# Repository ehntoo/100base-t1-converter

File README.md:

# 100base-t1-converter

This project provides a media converter for connecting 100Base-TX ethernet to
100Base-T1 (Automotive Ethernet) networks, using an NXP TJA1101 PHY. This part
doesn't have a whole lot of officially-available documentation, but is
significantly cheaper than the previous-generation TJA1100. Sufficient
information to use the chip in a design was assembled from various NXP (and
other) schematics online, such as the NXP schematics for the S32K148-T-BOX EVK.

Additional information for debugging was sourced from the Linux TJA11xx PHY
drivers.

The 100Base-TX PHY used is a CoreChips SR8201F (Realtek RTL8201F compatible),
sourceable from LCSC for ~$0.25 in reasonable quantities.

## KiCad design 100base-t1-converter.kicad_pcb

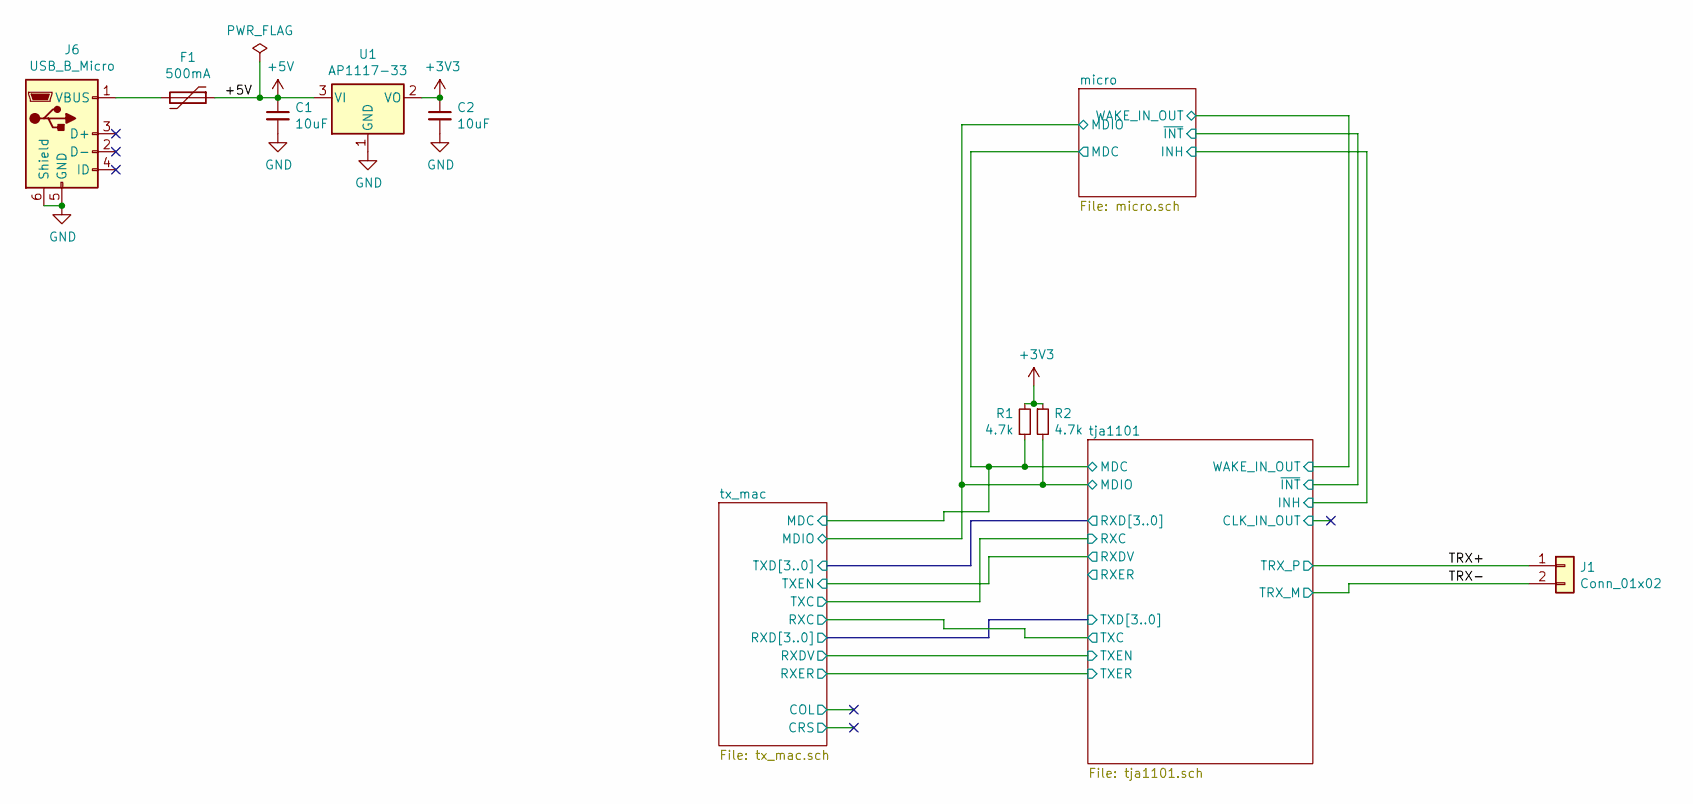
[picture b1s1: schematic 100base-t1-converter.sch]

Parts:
C1, C2: 10uF; C_0603_1608Metric_Pad1.05x0.95mm_HandSolder
F1: 500mA; Fuse_0805_2012Metric_Pad1.15x1.40mm_HandSolder
J1: Conn_01x02; SIP-2
J6: USB_B_Micro; LCSC_C77238
R1, R2: 4.7k; R_0603_1608Metric_Pad1.05x0.95mm_HandSolder
U1: AP1117-33; SOT-223-3_TabPin2

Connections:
+3V3: C2.1, R1.2, R2.1, U1.2 (VO); also elsewhere on the board
+5V: C1.1, F1.1, U1.3 (VI); also elsewhere on the board
/TRX+: J1.1; also elsewhere on the board
/TRX-: J1.2; also elsewhere on the board
/micro/MDC: R1.1; also elsewhere on the board
/micro/MDIO: R2.2; also elsewhere on the board
GND: C1.2, C2.2, J6.5 (GND), J6.6 (Shield), U1.1 (GND); also elsewhere on the board
unnamed: F1.2, J6.1 (VBUS)

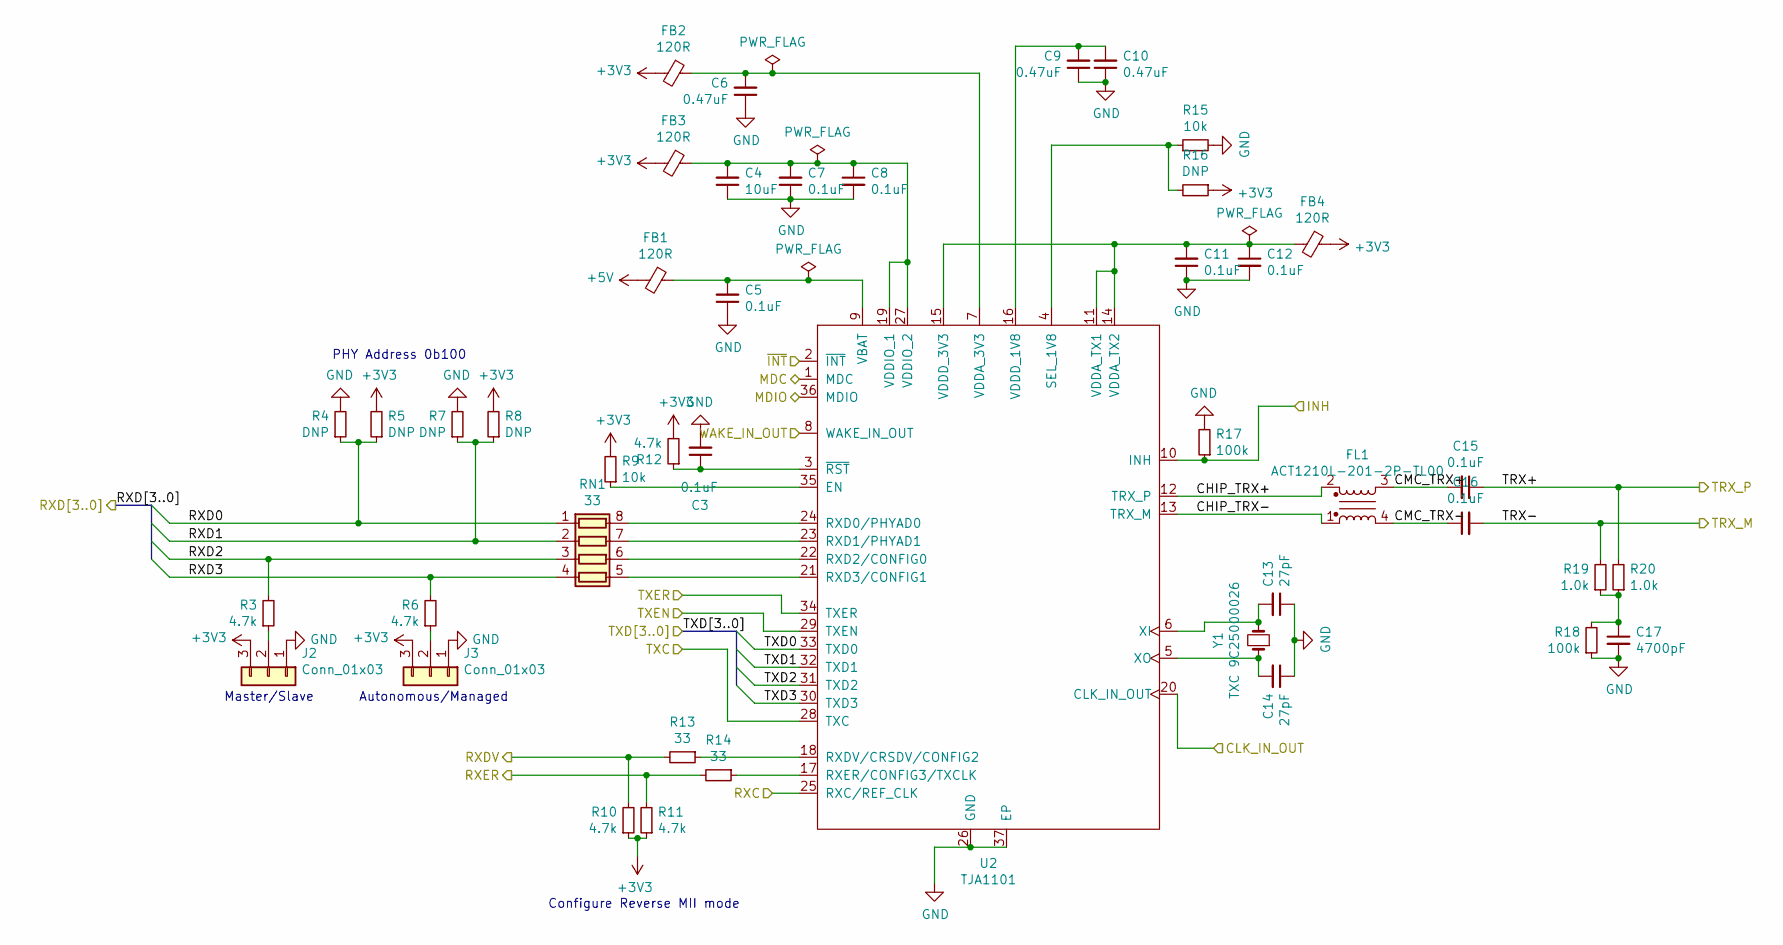
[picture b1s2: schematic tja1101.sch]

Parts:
C3, C5, C7, C8, C11, C12, C15, C16: 0.1uF; C_0603_1608Metric_Pad1.05x0.95mm_HandSolder
C4: 10uF; C_0603_1608Metric_Pad1.05x0.95mm_HandSolder
C6, C9, C10: 0.47uF; C_0603_1608Metric_Pad1.05x0.95mm_HandSolder
C13, C14: 27pF; C_0603_1608Metric_Pad1.05x0.95mm_HandSolder
C17: 4700pF; C_0603_1608Metric_Pad1.05x0.95mm_HandSolder
FB1, FB2, FB3, FB4: 120R; L_0603_1608Metric_Pad1.05x0.95mm_HandSolder
FL1: ACT1210L-201-2P-TL00; SOIC-4
J2, J3: Conn_01x03; PinSocket_1x03_P2.54mm_Vertical
R3, R6, R10, R11, R12: 4.7k; R_0603_1608Metric_Pad1.05x0.95mm_HandSolder
R4, R5, R7, R8, R16: DNP; R_0603_1608Metric_Pad1.05x0.95mm_HandSolder
R9, R15: 10k; R_0603_1608Metric_Pad1.05x0.95mm_HandSolder
R13, R14: 33; R_0603_1608Metric_Pad1.05x0.95mm_HandSolder
R17, R18: 100k; R_0603_1608Metric_Pad1.05x0.95mm_HandSolder
R19, R20: 1.0k; R_0603_1608Metric_Pad1.05x0.95mm_HandSolder
RN1: 33; R_Array_Convex_Reversed_4x0603
U2: TJA1101; QFN-36-1EP_6x6mm_P0.5mm_EP4.1x4.1mm_ThermalVias
Y1: TXC 9C25000026; Crystal_SMD_HC49-SD_HandSoldering

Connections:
+3V3: FB2.2, FB3.2, FB4.1, J2.3, J3.3, R5.2, R8.2, R9.2, R10.1, R11.1, R12.2, R16.1; also elsewhere on the board
+5V: FB1.2; also elsewhere on the board
/TRX+: C15.1, R20.2; also elsewhere on the board
/TRX-: C16.2, R19.2; also elsewhere on the board
/micro/INH: R17.1, U2.10 (INH); also elsewhere on the board
/micro/MDC: U2.1 (MDC); also elsewhere on the board
/micro/MDIO: U2.36 (MDIO); also elsewhere on the board
/micro/WAKE_IN_OUT: U2.8 (WAKE_IN_OUT); also elsewhere on the board
/micro/~INT: U2.2 (~INT); also elsewhere on the board
/tja1101/CHIP_TRX+: FL1.2, U2.12 (TRX_P)
/tja1101/CHIP_TRX-: FL1.1, U2.13 (TRX_M)
/tja1101/CLK_IN_OUT: U2.20 (CLK_IN_OUT)
/tja1101/CMC_TRX+: C15.2, FL1.3
/tja1101/CMC_TRX-: C16.1, FL1.4
/tja1101/RXC: U2.25 (RXC/REF_CLK); also elsewhere on the board
/tja1101/RXD0: R4.1, R5.1, RN1.1 (R1.1); also elsewhere on the board
/tja1101/RXD1: R7.1, R8.1, RN1.2 (R2.1); also elsewhere on the board
/tja1101/RXD2: R3.2, RN1.3 (R3.1); also elsewhere on the board
/tja1101/RXD3: R6.2, RN1.4 (R4.1); also elsewhere on the board
/tja1101/RXDV: R10.2, R13.2; also elsewhere on the board
/tja1101/RXER: R11.2, R14.2
/tx_mac/RXC: U2.28 (TXC); also elsewhere on the board
/tx_mac/RXD0: U2.33 (TXD0); also elsewhere on the board
/tx_mac/RXD1: U2.32 (TXD1); also elsewhere on the board
/tx_mac/RXD2: U2.31 (TXD2); also elsewhere on the board
/tx_mac/RXD3: U2.30 (TXD3); also elsewhere on the board
/tx_mac/RXDV: U2.29 (TXEN); also elsewhere on the board
/tx_mac/RXER: U2.34 (TXER); also elsewhere on the board
GND: C3.2, C4.1, C5.1, C6.1, C7.1, C8.2, C9.1, C10.1, C11.1, C12.2, C13.1, C14.1, C17.2, J2.1, J3.1, R4.2, R7.2, R15.2, R17.2, R18.1, U2.26 (GND), U2.37 (EP); also elsewhere on the board
unnamed: C3.1, R12.1, U2.3 (~RST)
unnamed: C4.2, C7.2, C8.1, FB3.1, U2.19 (VDDIO_1), U2.27 (VDDIO_2)
unnamed: C5.2, FB1.1, U2.9 (VBAT)
unnamed: C6.2, FB2.1, U2.7 (VDDA_3V3)
unnamed: C9.2, C10.2, U2.16 (VDDD_1V8)
unnamed: C11.2, C12.1, FB4.2, U2.11 (VDDA_TX1), U2.14 (VDDA_TX2), U2.15 (VDDD_3V3)
unnamed: C13.2, U2.6 (XI), Y1.2
unnamed: C14.2, U2.5 (XO), Y1.1
unnamed: C17.1, R18.2, R19.1, R20.1
unnamed: J2.2, R3.1
unnamed: J3.2, R6.1
unnamed: R9.1, U2.35 (EN)
unnamed: R13.1, U2.18 (RXDV/CRSDV/CONFIG2)
unnamed: R14.1, U2.17 (RXER/CONFIG3/TXCLK)
unnamed: R15.1, R16.2, U2.4 (SEL_1V8)
unnamed: RN1.5 (R4.2), U2.21 (RXD3/CONFIG1)
unnamed: RN1.6 (R3.2), U2.22 (RXD2/CONFIG0)
unnamed: RN1.7 (R2.2), U2.23 (RXD1/PHYAD1)
unnamed: RN1.8 (R1.2), U2.24 (RXD0/PHYAD0)

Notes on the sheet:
Configure Reverse MII mode
PHY Address 0b100
Master/Slave
Autonomous/Managed

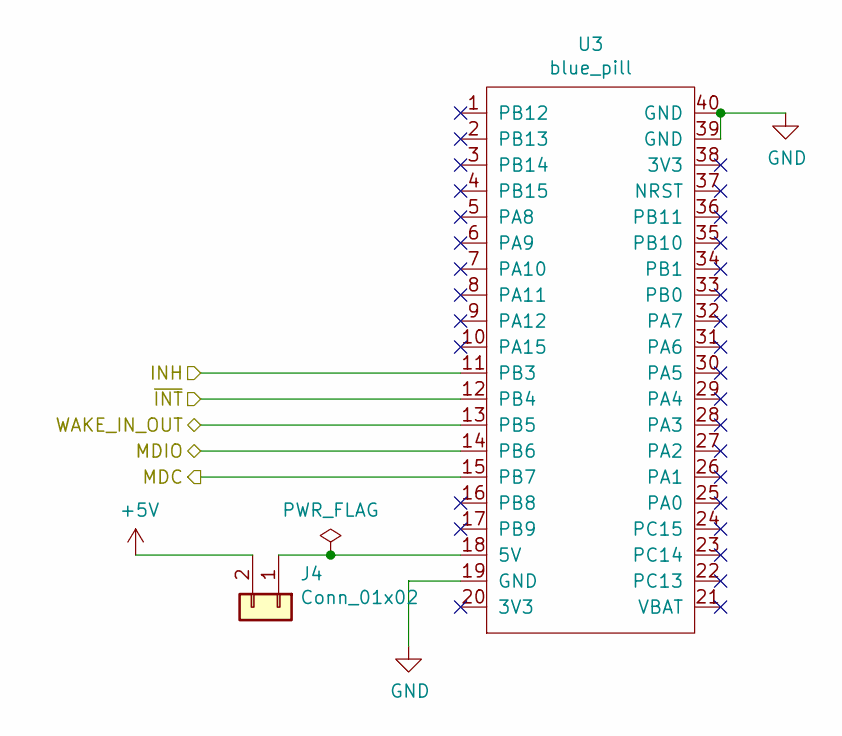
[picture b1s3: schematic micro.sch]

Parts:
J4: Conn_01x02; PinSocket_1x02_P2.54mm_Vertical
U3: blue_pill; DIP-40_W15.24mm

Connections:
+5V: J4.2; also elsewhere on the board
/micro/INH: U3.11 (PB3); also elsewhere on the board
/micro/MDC: U3.15 (PB7); also elsewhere on the board
/micro/MDIO: U3.14 (PB6); also elsewhere on the board
/micro/WAKE_IN_OUT: U3.13 (PB5); also elsewhere on the board
/micro/~INT: U3.12 (PB4); also elsewhere on the board
GND: U3.19 (GND), U3.39 (GND), U3.40 (GND); also elsewhere on the board
unnamed: J4.1, U3.18 (5V)

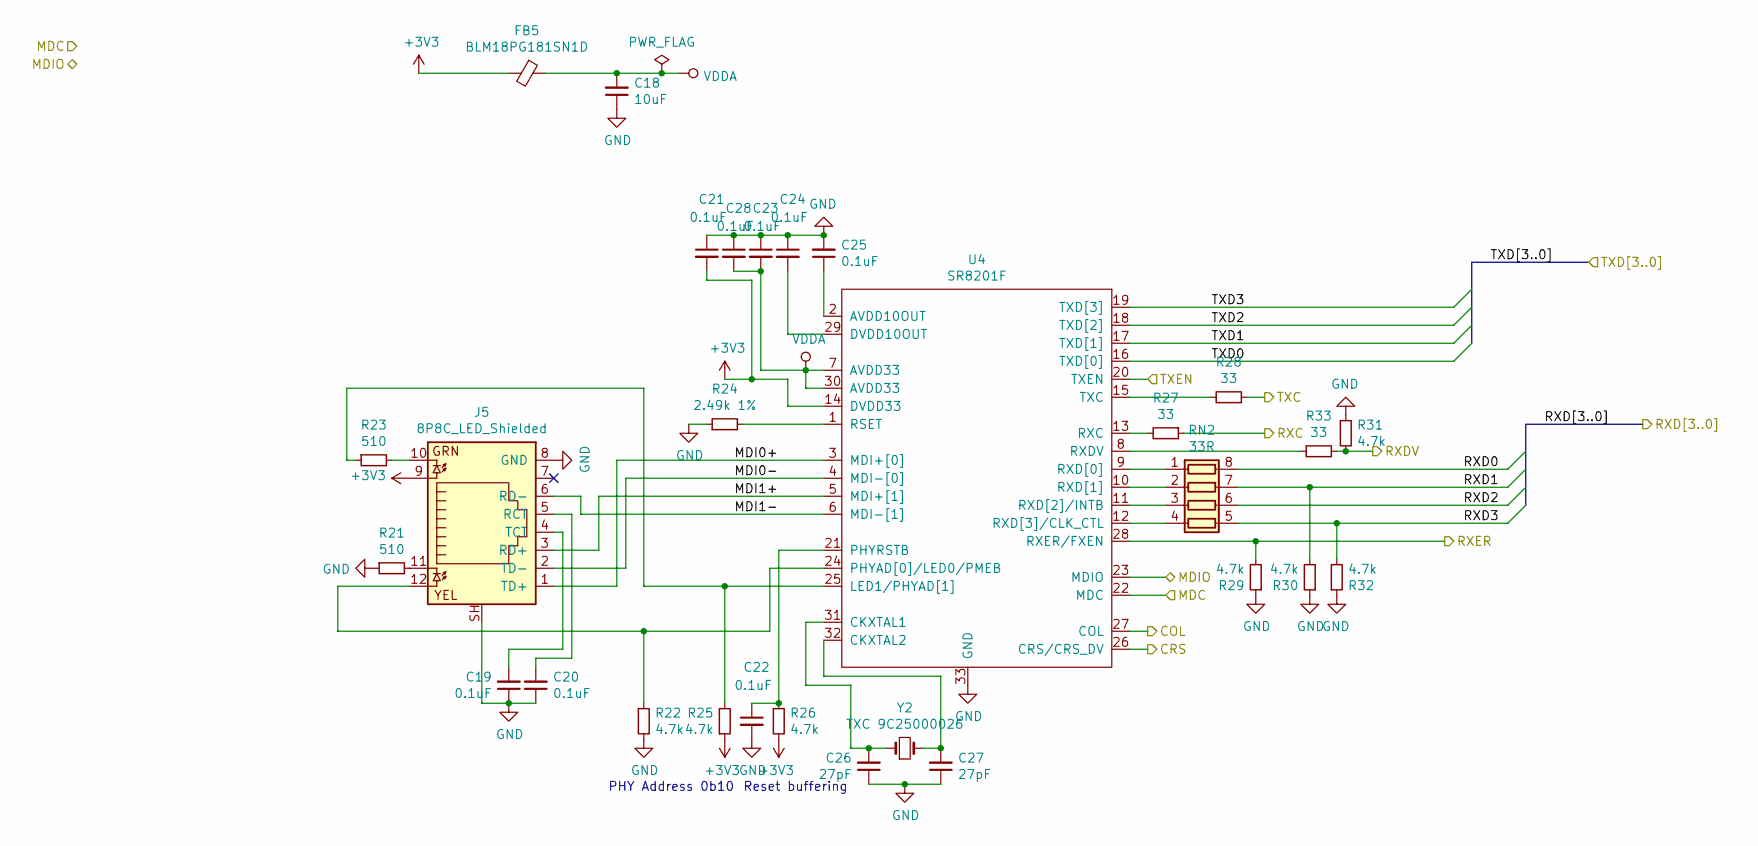
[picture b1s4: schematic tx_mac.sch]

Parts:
C18: 10uF; C_0603_1608Metric_Pad1.05x0.95mm_HandSolder
C19, C20, C21, C22, C23, C24, C25, C28: 0.1uF; C_0603_1608Metric_Pad1.05x0.95mm_HandSolder
C26, C27: 27pF; C_0603_1608Metric_Pad1.05x0.95mm_HandSolder
FB5: BLM18PG181SN1D; L_0603_1608Metric_Pad1.05x0.95mm_HandSolder
J5: 8P8C_LED_Shielded; RJ45_Hanrun_HR911105A
R21, R23: 510; R_0603_1608Metric_Pad1.05x0.95mm_HandSolder
R22, R25, R26, R29, R30, R31, R32: 4.7k; R_0603_1608Metric_Pad1.05x0.95mm_HandSolder
R24: 2.49k 1%; R_0603_1608Metric_Pad1.05x0.95mm_HandSolder
R27, R28, R33: 33; R_0603_1608Metric_Pad1.05x0.95mm_HandSolder
RN2: 33R; R_Array_Convex_Reversed_4x0603
U4: SR8201F; QFN-32-1EP_5x5mm_P0.5mm_EP3.6x3.6mm_ThermalVias
Y2: TXC 9C25000026; Crystal_SMD_HC49-SD_HandSoldering

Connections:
+3V3: C21.2, FB5.2, J5.9, R25.1, R26.2, U4.14 (DVDD33); also elsewhere on the board
/micro/MDC: U4.22 (MDC); also elsewhere on the board
/micro/MDIO: U4.23 (MDIO); also elsewhere on the board
/tja1101/RXC: R28.1; also elsewhere on the board
/tja1101/RXD0: U4.16 (TXD[0]); also elsewhere on the board
/tja1101/RXD1: U4.17 (TXD[1]); also elsewhere on the board
/tja1101/RXD2: U4.18 (TXD[2]); also elsewhere on the board
/tja1101/RXD3: U4.19 (TXD[3]); also elsewhere on the board
/tja1101/RXDV: U4.20 (TXEN); also elsewhere on the board
/tx_mac/COL: U4.27 (COL)
/tx_mac/CRS: U4.26 (CRS/CRS_DV)
/tx_mac/MDI0+: J5.1 (TD+), U4.3 (MDI+[0])
/tx_mac/MDI0-: J5.2 (TD-), U4.4 (MDI-[0])
/tx_mac/MDI1+: J5.3 (RD+), U4.5 (MDI+[1])
/tx_mac/MDI1-: J5.6 (RD-), U4.6 (MDI-[1])
/tx_mac/RXC: R27.1; also elsewhere on the board
/tx_mac/RXD0: RN2.8 (R1.2); also elsewhere on the board
/tx_mac/RXD1: R30.2, RN2.7 (R2.2); also elsewhere on the board
/tx_mac/RXD2: RN2.6 (R3.2); also elsewhere on the board
/tx_mac/RXD3: R32.2, RN2.5 (R4.2); also elsewhere on the board
/tx_mac/RXDV: R31.2, R33.1; also elsewhere on the board
/tx_mac/RXER: R29.2, U4.28 (RXER/FXEN); also elsewhere on the board
GND: C18.1, C19.1, C20.1, C21.1, C22.2, C23.1, C24.1, C25.2, C26.1, C27.1, C28.1, J5.8 (GND), J5.SH, R21.1, R22.2, R24.1, R29.1, R30.1, R31.1, R32.1, U4.33 (GND); also elsewhere on the board
unnamed: C19.2, J5.4 (TCT)
unnamed: C20.2, J5.5 (RCT)
unnamed: C22.1, R26.1, U4.21 (PHYRSTB)
unnamed: C24.2, U4.29 (DVDD10OUT)
unnamed: C25.1, U4.2 (AVDD10OUT)
unnamed: C26.2, U4.31 (CKXTAL1), Y2.1
unnamed: C27.2, U4.32 (CKXTAL2), Y2.2
unnamed: J5.10, R23.2
unnamed: J5.11, R21.2
unnamed: J5.12, R22.1, U4.24 (PHYAD[0]/LED0/PMEB)
unnamed: R23.1, R25.2, U4.25 (LED1/PHYAD[1])
unnamed: R24.2, U4.1 (RSET)
unnamed: R27.2, U4.13 (RXC)
unnamed: R28.2, U4.15 (TXC)
unnamed: R33.2, U4.8 (RXDV)
unnamed: RN2.1 (R1.1), U4.9 (RXD[0])
unnamed: RN2.2 (R2.1), U4.10 (RXD[1])
unnamed: RN2.3 (R3.1), U4.11 (RXD[2]/INTB)
unnamed: RN2.4 (R4.1), U4.12 (RXD[3]/CLK_CTL)
VDDA: C18.2, C23.2, C28.2, FB5.1, U4.7 (AVDD33), U4.30 (AVDD33)

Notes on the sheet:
PHY Address 0b10
Reset buffering

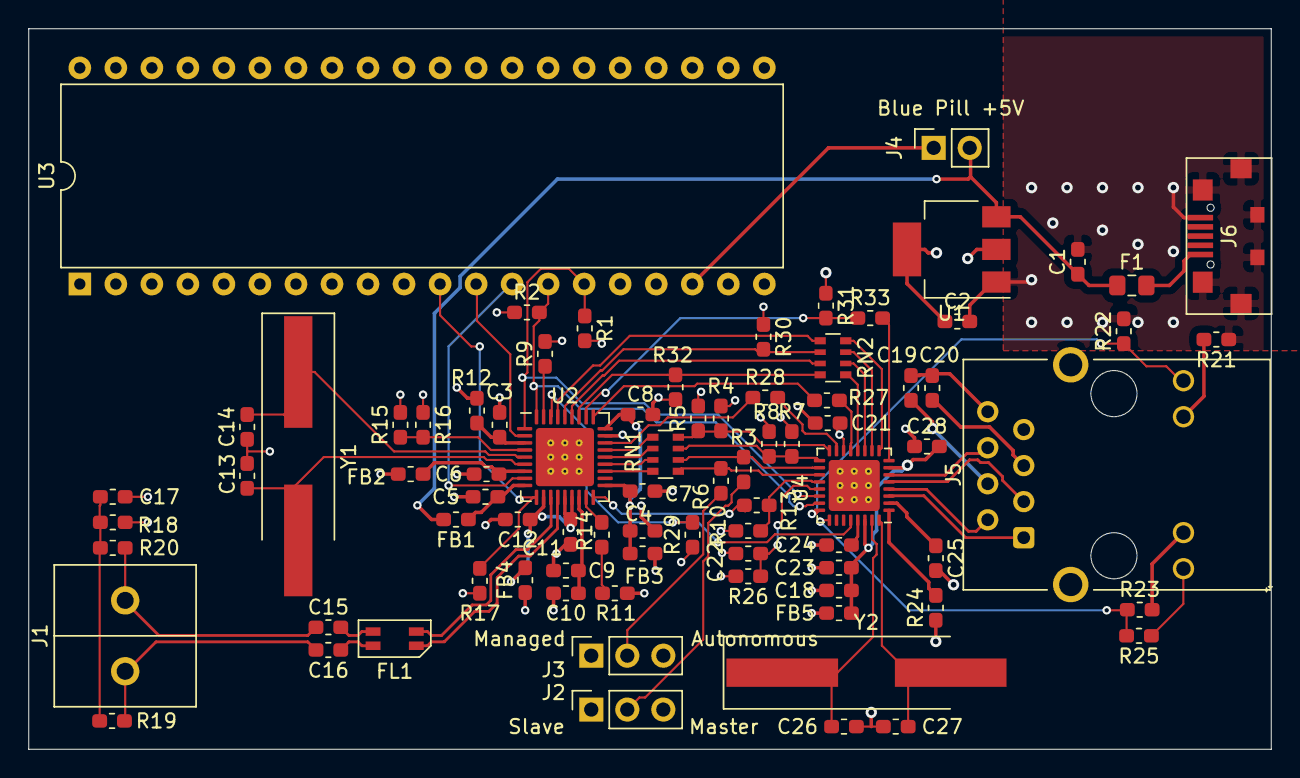
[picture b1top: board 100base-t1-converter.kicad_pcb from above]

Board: 4 copper layers, 87.6 x 50.8 mm, 82 parts (0 on the bottom side), 73 nets.

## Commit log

2020-11-28 Add README
2020-11-28 Add LICENSE

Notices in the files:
100base-t1-converter.kicad_pcb:
Copyright Mitchell Johnson 2019
Licensed CC-BY-SA
